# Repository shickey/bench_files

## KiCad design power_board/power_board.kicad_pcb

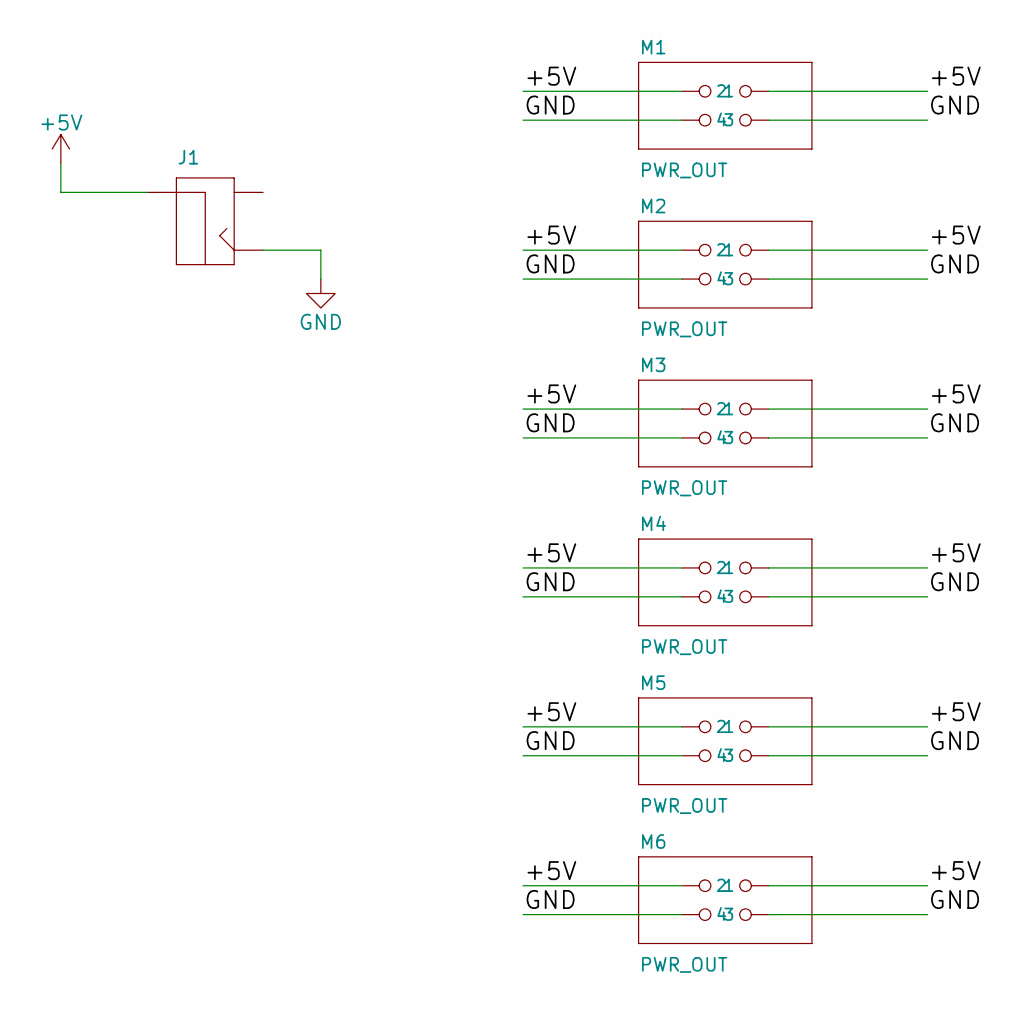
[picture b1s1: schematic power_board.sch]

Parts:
J1: JACK2.1MM; fab-JACK_2.1MM
M1, M2, M3, M4, M5, M6: PWR_OUT; fab-2X02SMD

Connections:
+5V: J1.PIN, M1.1, M1.2, M2.1, M2.2, M3.1, M3.2, M4.1, M4.2, M5.1, M5.2, M6.1, M6.2
GND: J1.CONT (CONTACT), M1.3, M1.4, M2.3, M2.4, M3.3, M3.4, M4.3, M4.4, M5.3, M5.4, M6.3, M6.4

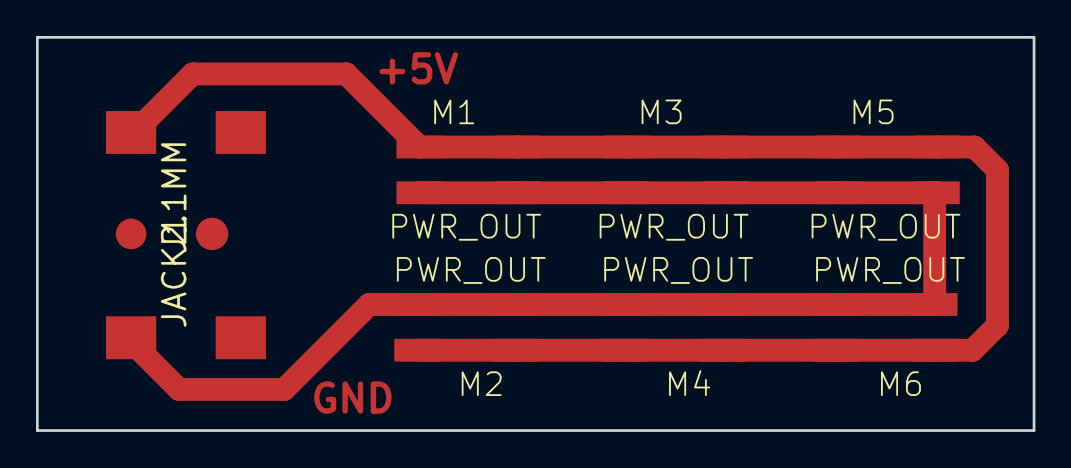
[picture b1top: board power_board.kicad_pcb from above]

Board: 2 copper layers, 55.4 x 21.8 mm, 7 parts (0 on the bottom side), 2 nets.

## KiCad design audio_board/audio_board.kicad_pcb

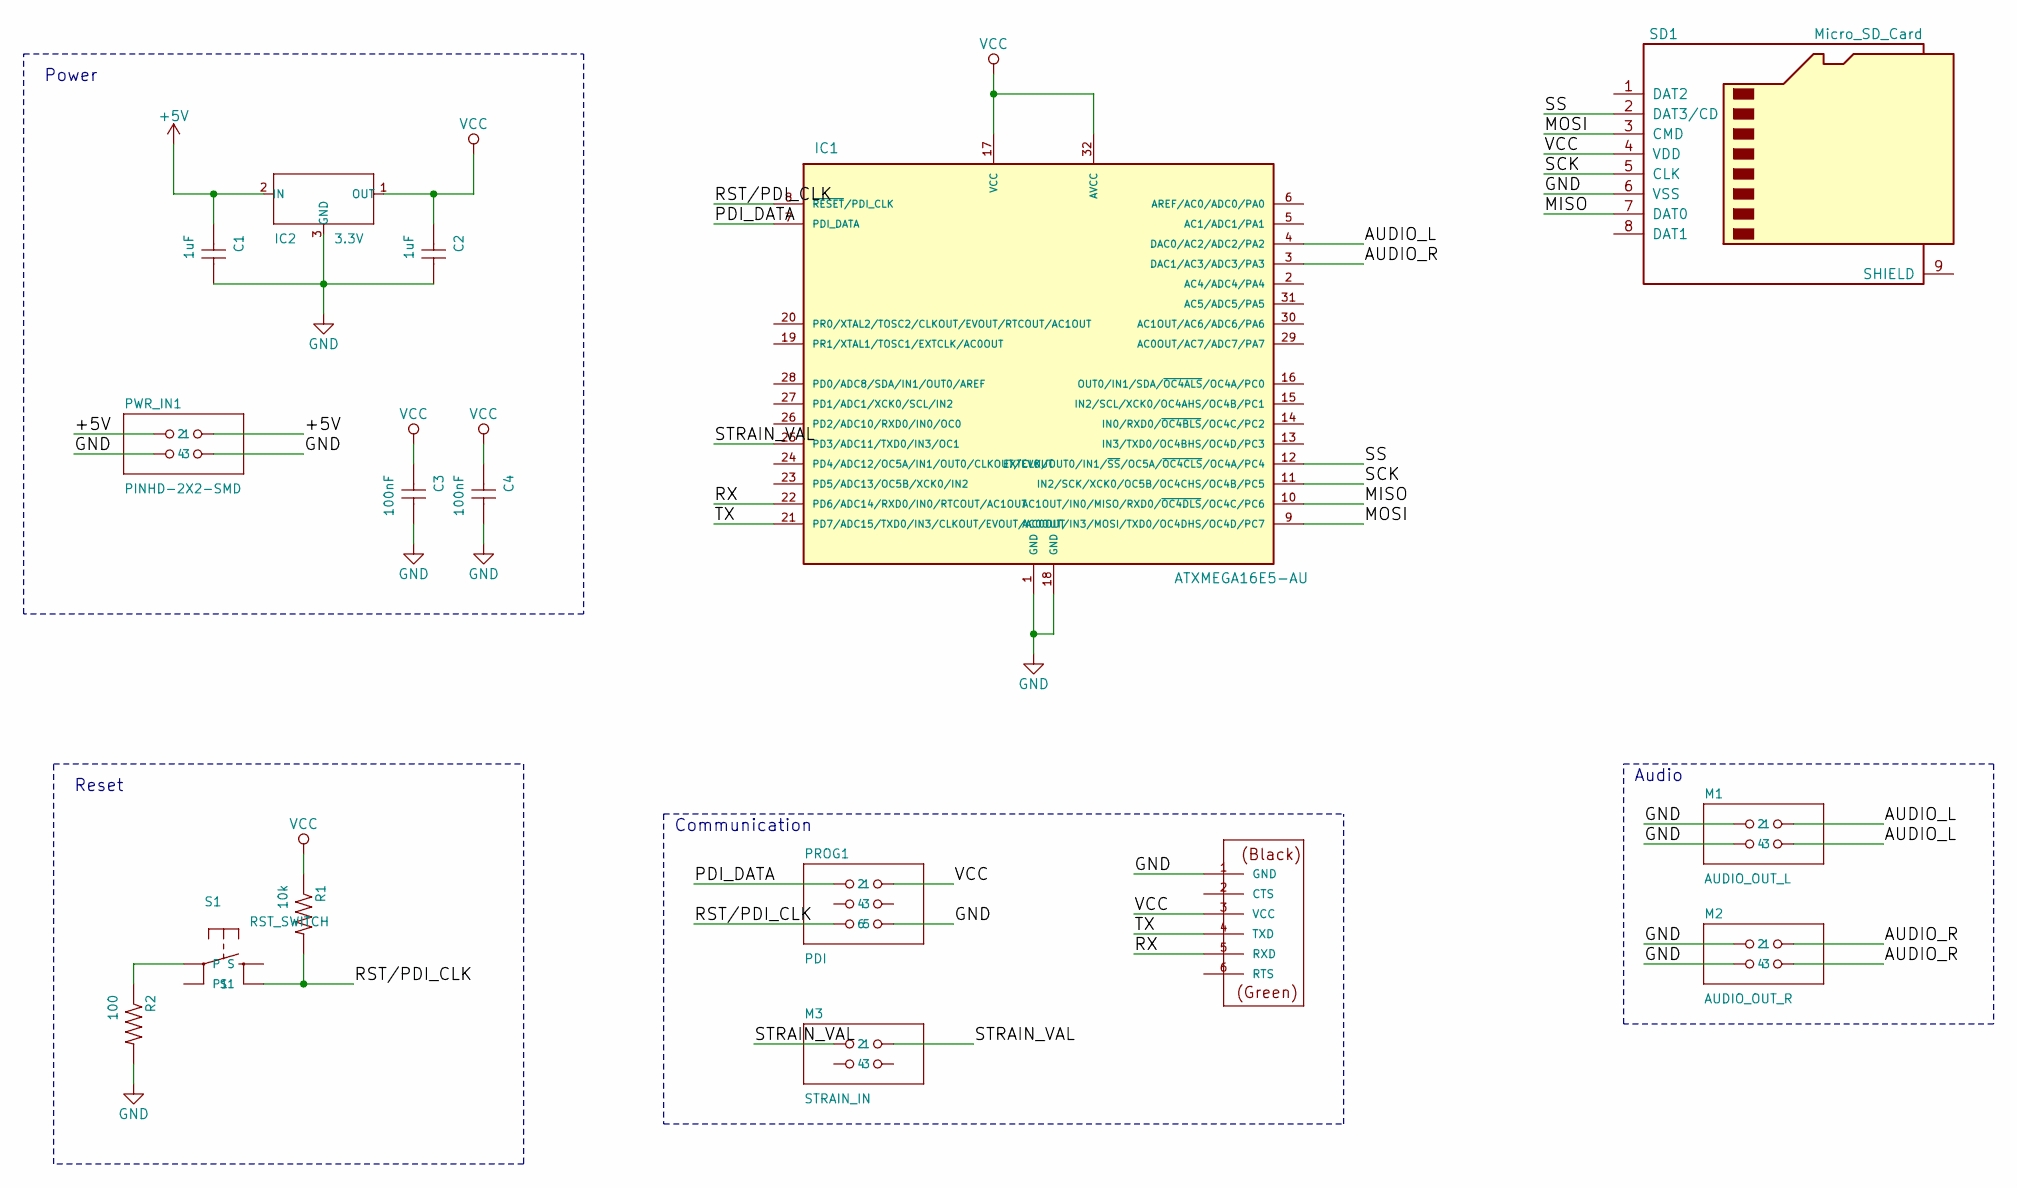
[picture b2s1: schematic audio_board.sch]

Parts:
C1, C2: 1uF; fab-C1206
C3, C4: 100nF; fab-C1206
FTDI1: FTDI-SMD-HEADER; fab-1X06SMD
IC1: ATXMEGA16E5-AU; fab-TQFP32-08THIN
IC2: 3.3V; fab-SOT23
M1: AUDIO_OUT_L; fab-2X02SMD
M2: AUDIO_OUT_R; fab-2X02SMD
M3: STRAIN_IN; fab-2X02SMD
PROG1: PDI; fab-2X03SMD
PWR_IN1: PINHD-2X2-SMD; fab-2X02SMD
R1: 10k; fab-R1206
R2: 100; fab-R1206
S1: RST_SWITCH; fab-6MM_SWITCH
SD1: Micro_SD_Card; MICROSD

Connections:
+5V: C1.1, IC2.2 (IN), PWR_IN1.1, PWR_IN1.2
/AUDIO_L: IC1.4 (DAC0/AC2/ADC2/PA2), M1.2, M1.4
/AUDIO_R: IC1.3 (DAC1/AC3/ADC3/PA3), M2.2, M2.4
/MISO: IC1.10 (AC1OUT/IN0/MISO/RXD0/~OC4DLS~/OC4C/PC6), SD1.7 (DAT0)
/MOSI: IC1.9 (AC0OUT/IN3/MOSI/TXD0/OC4DHS/OC4D/PC7), SD1.3 (CMD)
/PDI_DATA: IC1.7 (PDI_DATA), PROG1.1
/RST/PDI_CLK: IC1.8 (~RESET~/PDI_CLK), PROG1.5, R1.2, S1.4 (S1)
/RX: FTDI1.5 (RXD), IC1.22 (PD6/ADC14/RXD0/IN0/RTCOUT/AC1OUT)
/SCK: IC1.11 (IN2/SCK/XCK0/OC5B/OC4CHS/OC4B/PC5), SD1.5 (CLK)
/SS: IC1.12 (EXTCLK/OUT0/IN1/~SS~/OC5A/~OC4CLS~/OC4A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), SD1.2 (DAT3/CD)
/STRAIN_VAL: IC1.25 (PD3/ADC11/TXD0/IN3/OC1), M3.1, M3.2
/TX: FTDI1.4 (TXD), IC1.21 (PD7/ADC15/TXD0/IN3/CLKOUT/EVOUT/AC0OUT)
GND: C1.2, C2.2, C3.2, C4.2, FTDI1.1 (GND), IC1.1 (GND), IC1.18 (GND), IC2.3 (GND), M1.1, M1.3, M2.1, M2.3, PROG1.6, PWR_IN1.3, PWR_IN1.4, R2.2, SD1.6 (VSS); also elsewhere on the board
unnamed: R2.1, S1.1
VCC: C2.1, C3.1, C4.1, FTDI1.3 (VCC), IC1.17 (VCC), IC1.32 (AVCC), IC2.1 (OUT), PROG1.2, R1.1, SD1.4 (VDD)

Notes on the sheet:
Communication
Audio
Power
Reset

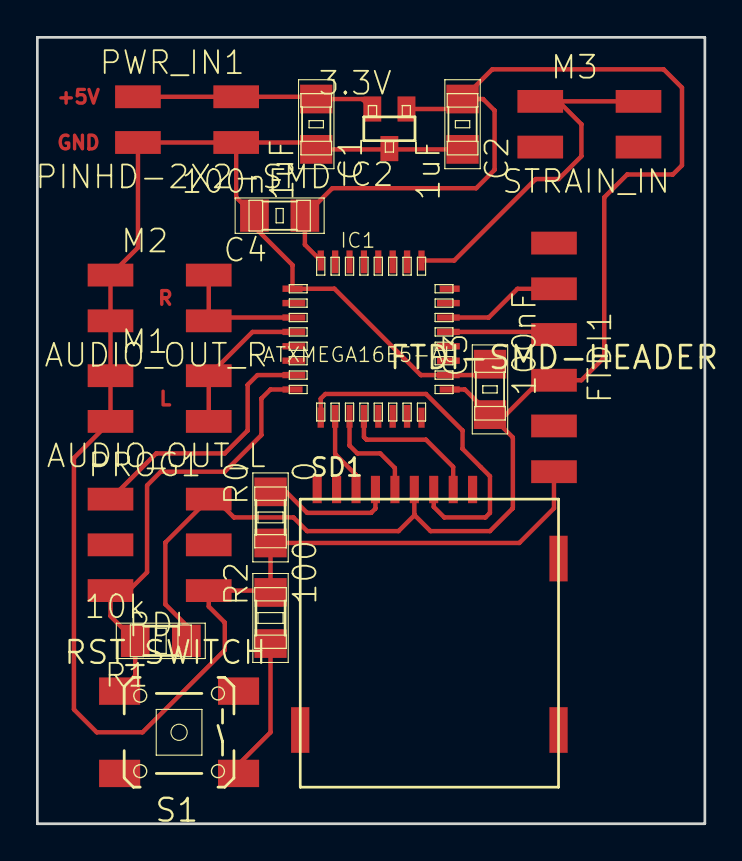
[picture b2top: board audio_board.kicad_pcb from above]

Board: 2 copper layers, 37.1 x 43.7 mm, 17 parts (0 on the bottom side), 15 nets.

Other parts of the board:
R0: 0; fab-R1206

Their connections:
GND: R0.1, R0.2; also elsewhere on the board

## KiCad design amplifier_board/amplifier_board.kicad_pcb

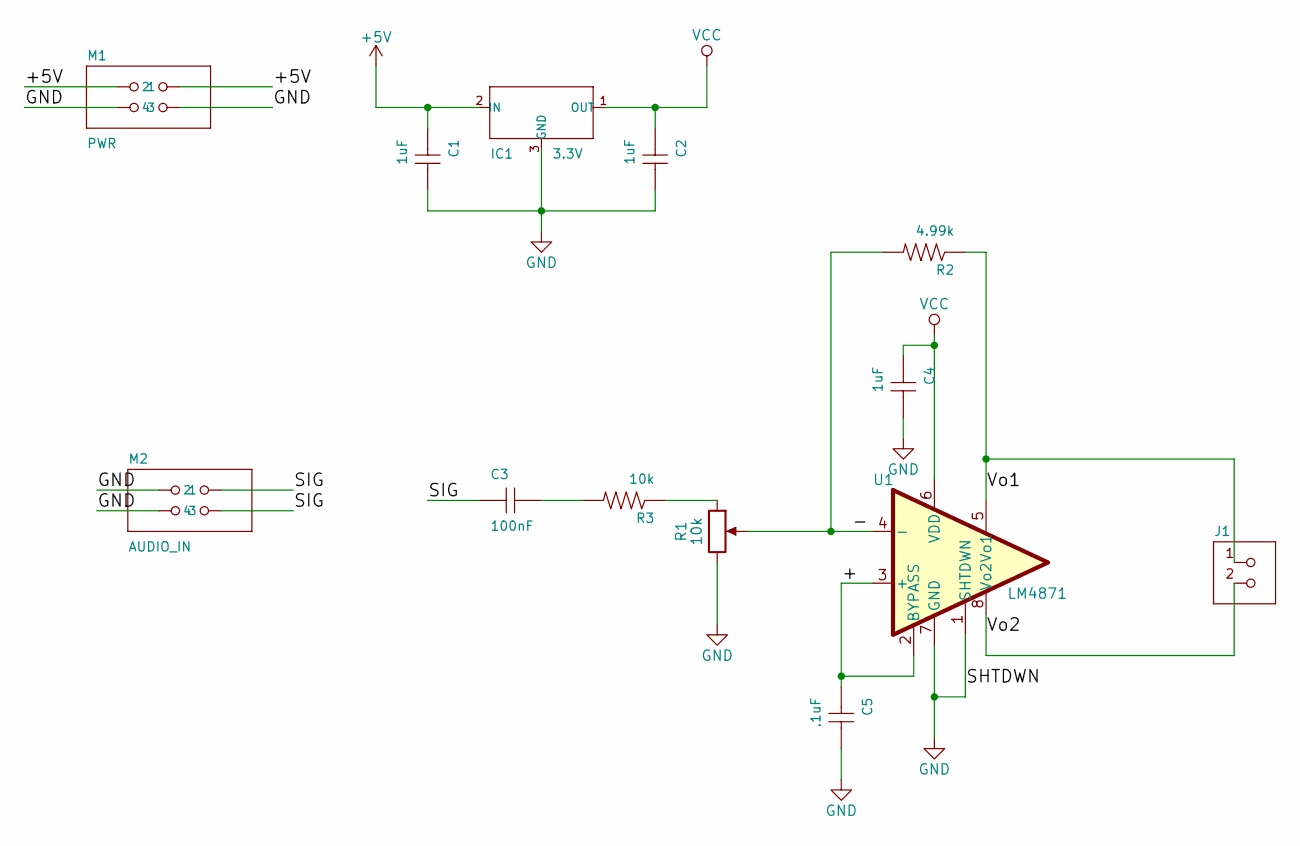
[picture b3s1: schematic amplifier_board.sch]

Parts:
C1, C2, C4: 1uF; fab-C1206
C3: 100nF; fab-C1206
C5: .1uF; fab-C1206
IC1: 3.3V; SOT-223
J1: 8_OHM_SPKR; fab-ED555DS-2DS
M1: PWR; fab-2X02SMD
M2: AUDIO_IN; fab-2X02SMD
R1: 10k; POT-PVZ2A
R2: 4.99k; fab-R1206
R3: 10k; fab-R1206
U1: LM4871; SOIC-8_3.9x4.9mm_Pitch1.27mm

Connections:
+5V: C1.1, IC1.2 (IN), M1.1, M1.2
/+: C5.1, U1.2 (BYPASS), U1.3 (+)
/-: R1.2, R2.2, U1.4 (-)
/SIG: C3.1, M2.2, M2.4
/Vo1: J1.1, R2.1, U1.5 (Vo1)
/Vo2: J1.2, U1.8 (Vo2)
GND: C1.2, C2.2, C4.2, C5.2, IC1.3 (GND), M1.3, M1.4, M2.1, M2.3, R1.3, U1.1 (SHTDWN), U1.7 (GND)
unnamed: C3.2, R3.2
unnamed: R1.1, R3.1
VCC: C2.1, C4.1, IC1.1 (OUT), U1.6 (VDD)

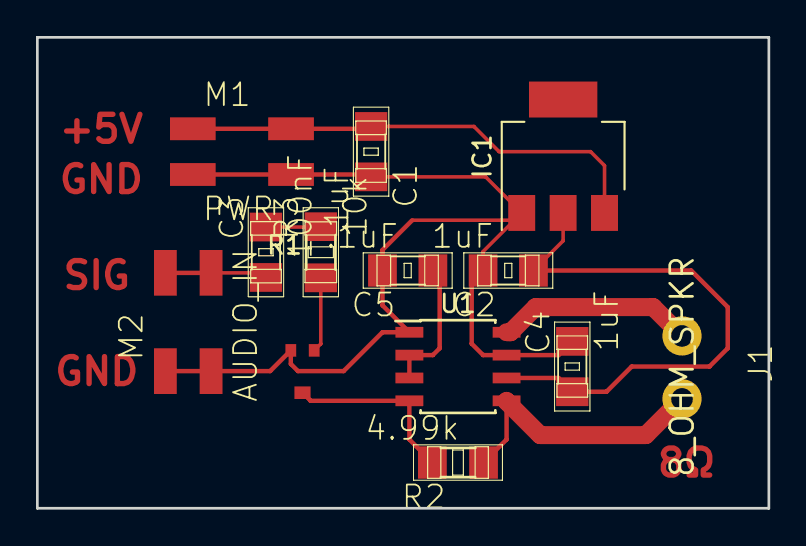
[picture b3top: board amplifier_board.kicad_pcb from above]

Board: 2 copper layers, 40.6 x 26.2 mm, 13 parts (0 on the bottom side), 10 nets.

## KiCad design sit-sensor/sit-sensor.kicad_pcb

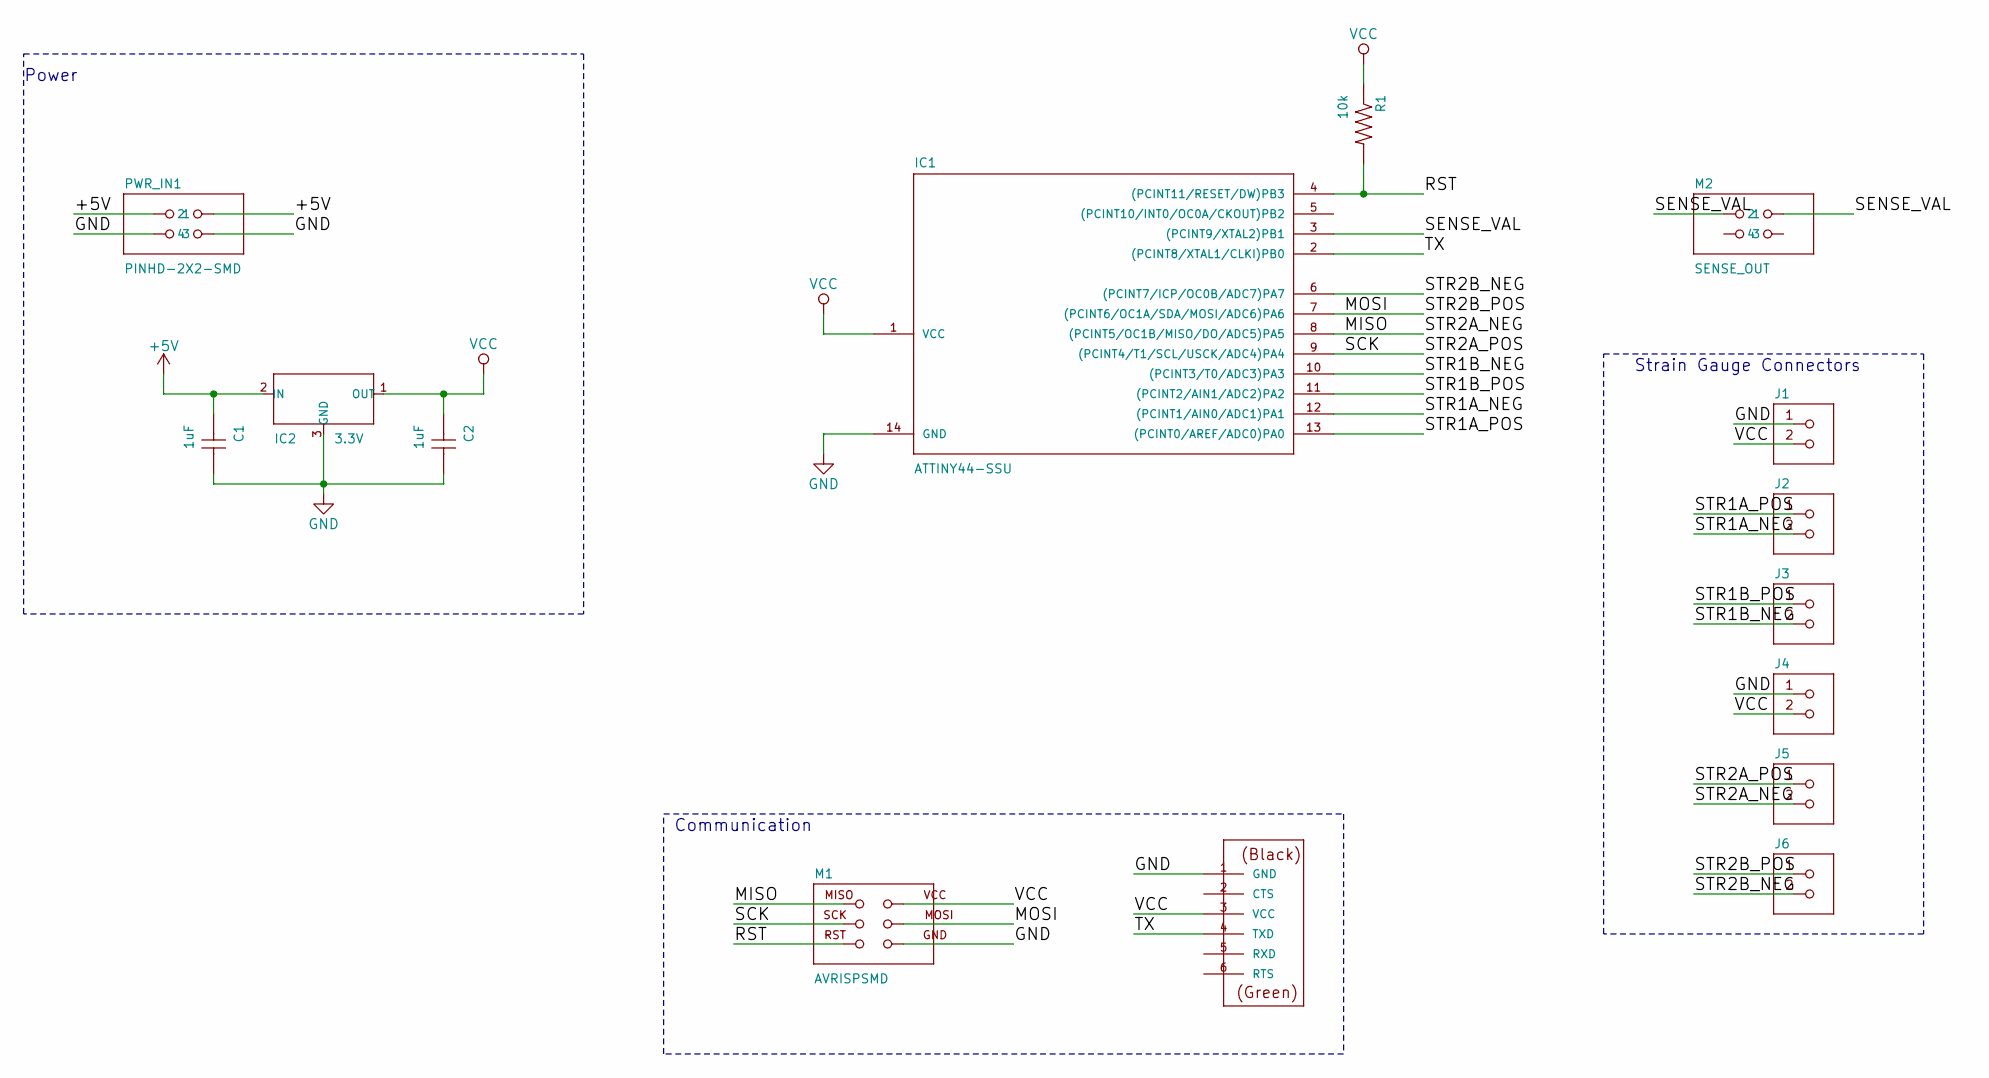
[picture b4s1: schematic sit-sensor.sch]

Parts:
C1, C2: 1uF; fab-C1206
FTDI1: FTDI-SMD-HEADER; fab-1X06SMD
IC1: ATTINY44-SSU; fab-SOIC14
IC2: 3.3V; fab-SOT23
J1, J4: STR_PWR; fab-3.5MMTERM
J2, J5: STRA; fab-3.5MMTERM
J3, J6: STRB; fab-3.5MMTERM
M1: AVRISPSMD; fab-2X03SMD
M2: SENSE_OUT; fab-2X02SMD
PWR_IN1: PINHD-2X2-SMD; fab-2X02SMD
R1: 10k; fab-R1206

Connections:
+5V: C1.1, IC2.2 (IN), PWR_IN1.1, PWR_IN1.2
/MISO: IC1.8 ((PCINT5/OC1B/MISO/DO/ADC5)PA5), J5.2, M1.1 (MISO)
/MOSI: IC1.7 ((PCINT6/OC1A/SDA/MOSI/ADC6)PA6), J6.1, M1.4 (MOSI)
/RST: IC1.4 ((PCINT11/RESET/DW)PB3), M1.5 (RST), R1.2
/SCK: IC1.9 ((PCINT4/T1/SCL/USCK/ADC4)PA4), J5.1, M1.3 (SCK)
/SENSE_VAL: IC1.3 ((PCINT9/XTAL2)PB1), M2.1, M2.2
/STR1A_NEG: IC1.12 ((PCINT1/AIN0/ADC1)PA1), J2.2
/STR1A_POS: IC1.13 ((PCINT0/AREF/ADC0)PA0), J2.1
/STR1B_NEG: IC1.10 ((PCINT3/T0/ADC3)PA3), J3.2
/STR1B_POS: IC1.11 ((PCINT2/AIN1/ADC2)PA2), J3.1
/STR2B_NEG: IC1.6 ((PCINT7/ICP/OC0B/ADC7)PA7), J6.2
/TX: FTDI1.4 (TXD), IC1.2 ((PCINT8/XTAL1/CLKI)PB0)
GND: C1.2, C2.2, FTDI1.1 (GND), IC1.14 (GND), IC2.3 (GND), J1.1, J4.1, M1.6 (GND), PWR_IN1.3, PWR_IN1.4
VCC: C2.1, FTDI1.3 (VCC), IC1.1 (VCC), IC2.1 (OUT), J1.2, J4.2, M1.2 (VCC), R1.1

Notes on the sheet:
Communication
Strain Gauge Connectors
Power

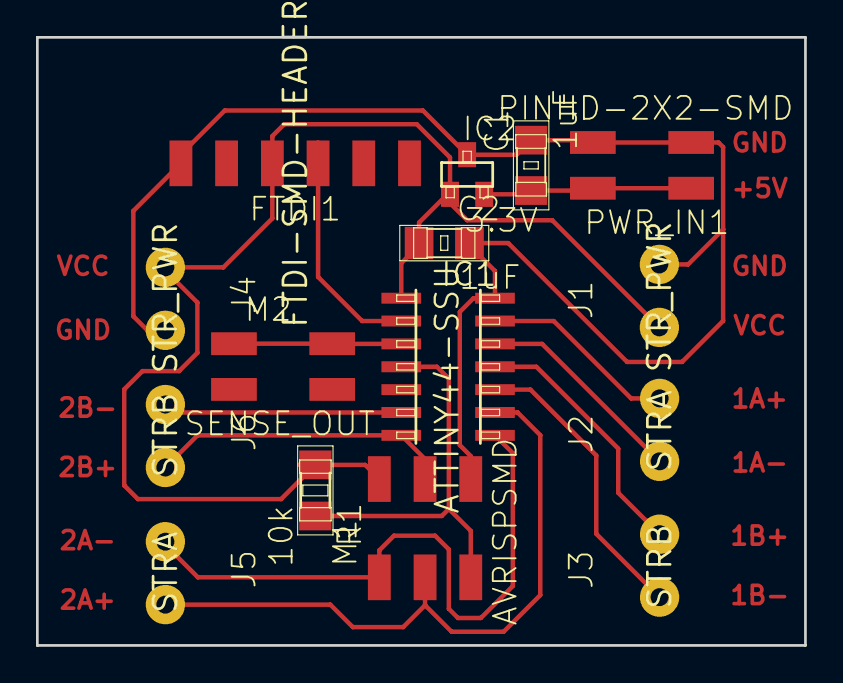
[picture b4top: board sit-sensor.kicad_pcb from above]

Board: 2 copper layers, 42.7 x 33.8 mm, 15 parts (0 on the bottom side), 14 nets.

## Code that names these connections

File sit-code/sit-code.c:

//
// hello.txrx.45.c
//
// step response transmit-receive hello-world
//    9600 baud FTDI interface
//
// Neil Gershenfeld
// 11/6/11
//
// (c) Massachusetts Institute of Technology 2011
// This work may be reproduced, modified, distributed,
// performed, and displayed for any purpose. Copyright is
// retained and must be preserved. The work is provided
// as is; no warranty is provided, and users accept all 
// liability.
//

#include <avr/io.h>
#include <util/delay.h>

#define output(directions,pin) (directions |= pin) // set port direction for output
#define set(port,pin) (port |= pin) // set port pin
#define clear(port,pin) (port &= (~pin)) // clear port pin
#define pin_test(pins,pin) (pins & pin) // test for port pin
#define bit_test(byte,bit) (byte & (1 << bit)) // test for bit set
#define bit_delay_time 102 // bit delay for 9600 with overhead
#define bit_delay() _delay_us(bit_delay_time) // RS232 bit delay
#define half_bit_delay() _delay_us(bit_delay_time/2) // RS232 half bit delay
#define settle_delay() _delay_us(100) // settle delay
#define char_delay() _delay_ms(10) // char delay

#define serial_port PORTB
#define serial_direction DDRB
#define serial_pin_out (1 << PB0)
#define sensor_out (1 << PB1)

// Calibration Values
#define ONE_A_OFFSET 0
#define ONE_B_OFFSET -20
#define TWO_A_OFFSET 0
#define TWO_B_OFFSET 0

void put_char(volatile unsigned char *port, unsigned char pin, char txchar) {
   //
   // send character in txchar on port pin
   //    assumes line driver (inverts bits)
   //
   // start bit
   //
   clear(*port,pin);
   bit_delay();
   //
   // unrolled loop to write data bits
   //
   if bit_test(txchar,0)
   set(*port,pin);
   else
   clear(*port,pin);
   bit_delay();
   if bit_test(txchar,1)
   set(*port,pin);
   else
   clear(*port,pin);
   bit_delay();
   if bit_test(txchar,2)
   set(*port,pin);
   else
   clear(*port,pin);
   bit_delay();
   if bit_test(txchar,3)
   set(*port,pin);
   else
   clear(*port,pin);
   bit_delay();
   if bit_test(txchar,4)
   set(*port,pin);
   else
   clear(*port,pin);
   bit_delay();
   if bit_test(txchar,5)
   set(*port,pin);
   else
   clear(*port,pin);
   bit_delay();
   if bit_test(txchar,6)
   set(*port,pin);
   else
   clear(*port,pin);
   bit_delay();
   if bit_test(txchar,7)
   set(*port,pin);
   else
   clear(*port,pin);
   bit_delay();
   //
   // stop bit
   //
   set(*port,pin);
   bit_delay();
   //
   // char delay
   //
   bit_delay();
}



#define SIT_THRESHOLD_ONE 25
#define SIT_THRESHOLD_TWO 25

static volatile uint16_t val1A = 0;
static volatile uint16_t val1B = 0;
static volatile uint16_t val2A = 0;
static volatile uint16_t val2B = 0;

int main(void) {
    //
    // main
    //

    //
    // set clock divider to /1
    //
    CLKPR = (1 << CLKPCE);
    CLKPR = (0 << CLKPS3) | (0 << CLKPS2) | (0 << CLKPS1) | (0 << CLKPS0);

    //
    // initialize output pins
    //
    set(serial_port, serial_pin_out);
    output(serial_direction, serial_pin_out);
    set(PORTB, sensor_out);
    output(DDRB, sensor_out);

   //
   // init A/D
   //
   ADMUX = (1 << REFS1) | (0 << REFS0); // Internal 1.1V ref (datasheet says don't use Vcc or AREF with differential ADC)
      // | (0 << ADLAR) // right adjust
      // | (0 << MUX5) | (0 << MUX4) | (1 << MUX3) | (0 << MUX2) | (0 << MUX1) | (1 << MUX0); // PA0 - PA1 difference (20x gain)
   ADCSRA = (1 << ADEN) // enable
      | (1 << ADPS2) | (1 << ADPS1) | (1 << ADPS0); // prescaler /128




    // Main loop

    while (1) {
        
        readSensors();

        uint16_t avg1 = (val1A + val1B) / 2;
        uint16_t avg2 = (val2A + val2B) / 2;

        if ((avg1 > SIT_THRESHOLD_ONE) && (avg2 > SIT_THRESHOLD_TWO)) {
            set(PORTB, sensor_out);
        }
        else {
            clear(PORTB, sensor_out);
        }



        //
        // send framing
        //
        put_char(&serial_port, serial_pin_out, 1);
        char_delay();
        put_char(&serial_port, serial_pin_out, 2);
        char_delay();
        put_char(&serial_port, serial_pin_out, 3);
        char_delay();
        put_char(&serial_port, serial_pin_out, 4);

        //
        // send result
        //
        put_char(&serial_port, serial_pin_out, (val1A & 0xFF));
        char_delay();
        put_char(&serial_port, serial_pin_out, ((val1A >> 8) & 0xFF));
        char_delay();
        put_char(&serial_port, serial_pin_out, (val1B & 0xFF));
        char_delay();
        put_char(&serial_port, serial_pin_out, ((val1B >> 8) & 0xFF));
        char_delay();
        put_char(&serial_port, serial_pin_out, (val2A & 0xFF));
        char_delay();
        put_char(&serial_port, serial_pin_out, ((val2A >> 8) & 0xFF));
        char_delay();
        put_char(&serial_port, serial_pin_out, (val2B & 0xFF));
        char_delay();
        put_char(&serial_port, serial_pin_out, ((val2B >> 8) & 0xFF));
        char_delay();
    }
}

inline void readSensors() {

        // PA0 - PA1 difference (20x gain)
        ADMUX = (1 << REFS1) | (0 << REFS0) | (0 << MUX5) | (0 << MUX4) | (1 << MUX3) | (0 << MUX2) | (0 << MUX1) | (1 << MUX0);
        //Start conversion
        ADCSRA |= (1 << ADSC);
        // Wait for completion
        while (ADCSRA & (1 << ADSC)) {
            ;
        }
        // Store the value
        val1A = ADC + ONE_A_OFFSET;
        if (val1A > 32767) { // Prevent negative rollover
          val1A = 0;
        }

        // PA2 - PA3 difference (20x gain)
        ADMUX = (1 << REFS1) | (0 << REFS0) | (0 << MUX5) | (1 << MUX4) | (0 << MUX3) | (0 << MUX2) | (0 << MUX1) | (1 << MUX0);
        ADCSRA |= (1 << ADSC);
        while (ADCSRA & (1 << ADSC)) {
            ;
        }
        val1B = ADC + ONE_B_OFFSET;
        if (val1B > 32767) {
          val1B = 0;
        }

        // PA4 - PA5 difference (20x gain)
        ADMUX = (1 << REFS1) | (0 << REFS0) | (0 << MUX5) | (1 << MUX4) | (1 << MUX3) | (0 << MUX2) | (1 << MUX1) | (1 << MUX0);
        ADCSRA |= (1 << ADSC);
        while (ADCSRA & (1 << ADSC)) {
            ;
        }
        val2A = ADC + TWO_A_OFFSET;
        if (val2A > 32767) {
          val2A = 0;
        }

        // PA6 - PA7 difference (20x gain)
        ADMUX = (1 << REFS1) | (0 << REFS0) | (0 << MUX5) | (1 << MUX4) | (1 << MUX3) | (1 << MUX2) | (1 << MUX1) | (1 << MUX0);
        ADCSRA |= (1 << ADSC);
        while (ADCSRA & (1 << ADSC)) {
            ;
        }
        val2B = ADC + TWO_B_OFFSET;
        if (val2B > 32767) {
          val2B = 0;
        }
    }

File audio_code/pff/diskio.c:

/*-------------------------------------------------------------------------*/
/* PFF - Low level disk control module for AVR							   */
/* Modified from (C)ChaN, 2014											   */
/*-------------------------------------------------------------------------*/

#include "pff.h"
#include "diskio.h"

/*-------------------------------------------------------------------------*/
/* Platform dependent macros and functions MODIFY FOR YOUR DEVICE           */
/*-------------------------------------------------------------------------*/

#include <util/delay.h>
#include <avr/io.h> /* Device specific include files */

#define SPIPORT PORTC
#define SPI_SCK (1 << 5)  /* PC5 */
#define SPI_MISO (1 << 6) /* PC6 SD card DO */
#define SPI_MOSI (1 << 7) /* PC7 SD card DI */
#define SPI_CS (1 << 4)   /* PC4 */

/* Port controls  (Platform dependent) */
#define SELECT() SPIPORT.OUTCLR   = SPI_CS /* CS = L */
#define DESELECT() SPIPORT.OUTSET = SPI_CS /* CS = H */
#define SELECTING ((SPIPORT.DIR & SPI_CS) && !(SPIPORT.OUT & SPI_CS))

 void init_spi(void)
{
	/* SPI pins */
	// PORTMUX.CTRLB    = PORTMUX_SPI0_ALTERNATE_gc;   /* Alternative comms location for SPI */
	SPIPORT.DIRSET   = SPI_MOSI | SPI_CS | SPI_SCK; /* Set outputs */
	SPIPORT.PIN6CTRL = PORT_OPC_PULLUP_gc;          /* Pull up on SPI_MISO (SD card DO) */

	SPIC.CTRL = SPI_MASTER_bm;// | SPI_PRESCALER0_bm; // prescale /16 (which gives 2MHz with 32MHz processor)
	/* Slave select pin controlled in software */
	SPIC.CTRLB = SPI_SSD_bm;
	/* SPI Enable */
	SPIC.CTRL |= SPI_ENABLE_bm;
}

 BYTE spi(BYTE d)
{
	SPIC.DATA = d;
	while (!(SPIC.STATUS & SPI_IF_bm))
		;
	return SPIC.DATA;
}

static void xmit_spi(BYTE d)
{
	spi(d);
}

static BYTE rcv_spi(void)
{
	return spi(0xFF);
}

/*--------------------------------------------------------------------------

   Module Private Functions

---------------------------------------------------------------------------*/

/* Definitions for MMC/SDC command */
#define CMD0 (0x40 + 0)    /* GO_IDLE_STATE */
#define CMD1 (0x40 + 1)    /* SEND_OP_COND (MMC) */
#define ACMD41 (0xC0 + 41) /* SEND_OP_COND (SDC) */
#define CMD8 (0x40 + 8)    /* SEND_IF_COND */
#define CMD16 (0x40 + 16)  /* SET_BLOCKLEN */
#define CMD17 (0x40 + 17)  /* READ_SINGLE_BLOCK */
#define CMD24 (0x40 + 24)  /* WRITE_BLOCK */
#define CMD55 (0x40 + 55)  /* APP_CMD */
#define CMD58 (0x40 + 58)  /* READ_OCR */

/* Card type flags (CardType) */
#define CT_MMC 0x01   /* MMC ver 3 */
#define CT_SD1 0x02   /* SD ver 1 */
#define CT_SD2 0x04   /* SD ver 2 */
#define CT_BLOCK 0x08 /* Block addressing */

BYTE CardType = 0;

/*-----------------------------------------------------------------------*/
/* Send a command packet to MMC                                          */
/*-----------------------------------------------------------------------*/
static BYTE send_cmd(BYTE  cmd, /* 1st byte (Start + Index) */
                     DWORD arg  /* Argument (32 bits) */
                     )
{
	BYTE n, res;

	if (cmd & 0x80) { /* ACMD<n> is the command sequence of CMD55-CMD<n> */
		cmd &= 0x7F;
		res = send_cmd(CMD55, 0);
		if (res > 1)
			return res;
	}

	/* Select the card */
	DESELECT();
	rcv_spi();
	SELECT();
	rcv_spi();

	/* Send a command packet */
	xmit_spi(cmd);               /* Start + Command index */
	xmit_spi((BYTE)(arg >> 24)); /* Argument[31..24] */
	xmit_spi((BYTE)(arg >> 16)); /* Argument[23..16] */
	xmit_spi((BYTE)(arg >> 8));  /* Argument[15..8] */
	xmit_spi((BYTE)arg);         /* Argument[7..0] */
	n = 0x01;                    /* Dummy CRC + Stop */
	if (cmd == CMD0)
		n = 0x95; /* Valid CRC for CMD0(0) */
	if (cmd == CMD8)
		n = 0x87; /* Valid CRC for CMD8(0x1AA) */
	xmit_spi(n);

	/* Receive a command response */
	n = 10; /* Wait for a valid response in timeout of 10 attempts */
	do {
		res = rcv_spi();
	} while ((res & 0x80) && --n);

	return res; /* Return with the response value */
}

/*--------------------------------------------------------------------------

   Public Functions

---------------------------------------------------------------------------*/

/*-----------------------------------------------------------------------*/
/* Initialize Disk Drive                                                 */
/*-----------------------------------------------------------------------*/

DSTATUS disk_initialize(void)
{
	BYTE n, cmd, ty, ocr[4];
	UINT tmr;

#if _USE_WRITE
	if (CardType && SELECTING)
		disk_writep(0, 0); /* Finalize write process if it is in progress */
#endif

	init_spi(); /* Initialize ports to control MMC */
	DESELECT();
	for (n = 10; n; n--)
		rcv_spi(); /* 80 dummy clocks with CS=H */

	ty = 0;
	if (send_cmd(CMD0, 0) == 1) {         /* GO_IDLE_STATE */
		if (send_cmd(CMD8, 0x1AA) == 1) { /* SDv2 */
			for (n     = 0; n < 4; n++)
				ocr[n] = rcv_spi();                 /* Get trailing return value of R7 resp */
			if (ocr[2] == 0x01 && ocr[3] == 0xAA) { /* The card can work at vdd range of 2.7-3.6V */
				for (tmr = 10000; tmr && send_cmd(ACMD41, 1UL << 30); tmr--)
					_delay_us(100);                   /* Wait for leaving idle state (ACMD41 with HCS bit) */
				if (tmr && send_cmd(CMD58, 0) == 0) { /* Check CCS bit in the OCR */
					for (n     = 0; n < 4; n++)
						ocr[n] = rcv_spi();
					ty         = (ocr[0] & 0x40) ? CT_SD2 | CT_BLOCK : CT_SD2; /* SDv2 (HC or SC) */
				}
			}
		} else { /* SDv1 or MMCv3 */
			if (send_cmd(ACMD41, 0) <= 1) {
				ty  = CT_SD1;
				cmd = ACMD41; /* SDv1 */
			} else {
				ty  = CT_MMC;
				cmd = CMD1; /* MMCv3 */
			}
			for (tmr = 10000; tmr && send_cmd(cmd, 0); tmr--)
				_delay_us(100);                    /* Wait for leaving idle state */
			if (!tmr || send_cmd(CMD16, 512) != 0) /* Set R/W block length to 512 */
				ty = 0;
		}
	}
	CardType = ty;
	DESELECT();
	rcv_spi();

	return ty ? 0 : STA_NOINIT;
}

/*-----------------------------------------------------------------------*/
/* Read partial sector                                                   */
/*-----------------------------------------------------------------------*/

DRESULT disk_readp(BYTE *buff,   /* Pointer to the read buffer (NULL:Forward to the stream) */
                   DWORD sector, /* Sector number (LBA) */
                   UINT  offset, /* Byte offset to read from (0..511) */
                   UINT  count   /* Number of bytes to read (ofs + cnt mus be <= 512) */
                   )
{
	DRESULT res;
	BYTE    rc;
	UINT    bc;

	if (!(CardType & CT_BLOCK))
		sector *= 512; /* Convert to byte address if needed */

	res = RES_ERROR;
	if (send_cmd(CMD17, sector) == 0) { /* READ_SINGLE_BLOCK */

		// bc = 40000;	/* Time counter */
		do { /* Wait for response */
			rc = rcv_spi();
		} while (rc == 0xFF);

		if (rc == 0xFE) { /* A data packet arrived */

			bc = 512 + 2 - offset - count; /* Number of trailing bytes to skip */

			/* Skip leading bytes */
			while (offset--)
				rcv_spi();

			/* Receive a part of the sector */
			if (buff) { /* Store data to the memory */
				do {
					*buff++ = rcv_spi();
				} while (--count);
			} else { /* Forward data to the outgoing stream */
				do {
					// FORWARD(rcv_spi());
				} while (--count);
			}

			/* Skip trailing bytes and CRC */
			do
				rcv_spi();
			while (--bc);

			res = RES_OK;
		}
	}

	DESELECT();
	rcv_spi();

	return res;
}

/*-----------------------------------------------------------------------*/
/* Write partial sector                                                  */
/*-----------------------------------------------------------------------*/

#if _USE_WRITE
DRESULT disk_writep(const BYTE *buff, /* Pointer to the bytes to be written (NULL:Initiate/Finalize sector write) */
                    DWORD       sc    /* Number of bytes to send, Sector number (LBA) or zero */
                    )
{
	DRESULT     res;
	UINT        bc;
	static UINT wc; /* Sector write counter */

	res = RES_ERROR;

	if (buff) { /* Send data bytes */
		bc = sc;
		while (bc && wc) { /* Send data bytes to the card */
			xmit_spi(*buff++);
			wc--;
			bc--;
		}
		res = RES_OK;
	} else {
		if (sc) { /* Initiate sector write process */
			if (!(CardType & CT_BLOCK))
				sc *= 512;                  /* Convert to byte address if needed */
			if (send_cmd(CMD24, sc) == 0) { /* WRITE_SINGLE_BLOCK */
				xmit_spi(0xFF);
				xmit_spi(0xFE); /* Data block header */
				wc  = 512;      /* Set byte counter */
				res = RES_OK;
			}
		} else { /* Finalize sector write process */
			bc = wc + 2;
			while (bc--) {
				xmit_spi(0); /* Fill left bytes and CRC with zeros */
			}
			do {
				res = rcv_spi();
			} while (res == 0xFF);
			if ((res & 0x1F) == 0x05) { /* Receive data resp and wait for end of write process in timeout of 500ms */
				for (bc = 5000; rcv_spi() != 0xFF && bc; bc--) /* Wait for ready */
					_delay_us(100);
				if (bc)
					res = RES_OK;
			}
			DESELECT();
			rcv_spi();
		}
	}

	return res;
}
#endif

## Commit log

2017-12-15 Bench files
2017-12-18 Sketching out refactored audio and sit code (note: *neither* are working at the moment)
2017-12-18 Cleaned up audio code. Added fading, etc.
2017-12-19 Fixed up sit sensing code to be more accurate. Simplified audio code for performance reasons (for now)
